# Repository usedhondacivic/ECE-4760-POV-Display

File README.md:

# ECE-4760 Final Project: Persistence of Vision Display
A persistence of vision display constructed from scratch using the Raspberry Pi Pico W microcontroller. Runs at 30 FPS with full RGB color and streams images over wifi.

Created by: Michael Crum (mmc323@cornell.edu), Joseph Horwitz (jah569@cornell.edu), Rabail Makhdoom (rm857@cornell.edu)

Read the write up: https://michael-crum.com/pov_display/

Project structure:
 - /PICO
	 - main.c
		 - Code entry point on the pico
	 - /drivers/apa102
		- Driver for the SPI based APA102 LEDs
	 - /utils/picow_tcp_client.c
		 - Driver for the TCP client
 - /PYTHON
	 - wifi.py
		 - TCP server for sending image data
- /new_python
	- New experimental python setup, including a browser based interface and support for most image types including gif's
	- web_server.py
		- Entry point for the program, launches the webserver which serves the web interface on localhost port 8080 (localhost:8080 in your web browser)
	- tcp_server.py
		- Handles connecting to the display over TCP, and sending arbitry data over the connection
	- file_translation.py
		- Translates image data to a radial RGB format used by the display
	- display_driver.py
		- Handles the transition from a file name to the proper byte format, then sends packets to the display using functions from tcp_server.py
	-  index.html
		- The html file served by the browser client in web_server.py

 - /HARDWARE
	 - /CAD
		 - STL files for 3D printing the mechanical structure
	 - /ELECTRICAL
		 - KiCad project files for the rotor and control board PCBs

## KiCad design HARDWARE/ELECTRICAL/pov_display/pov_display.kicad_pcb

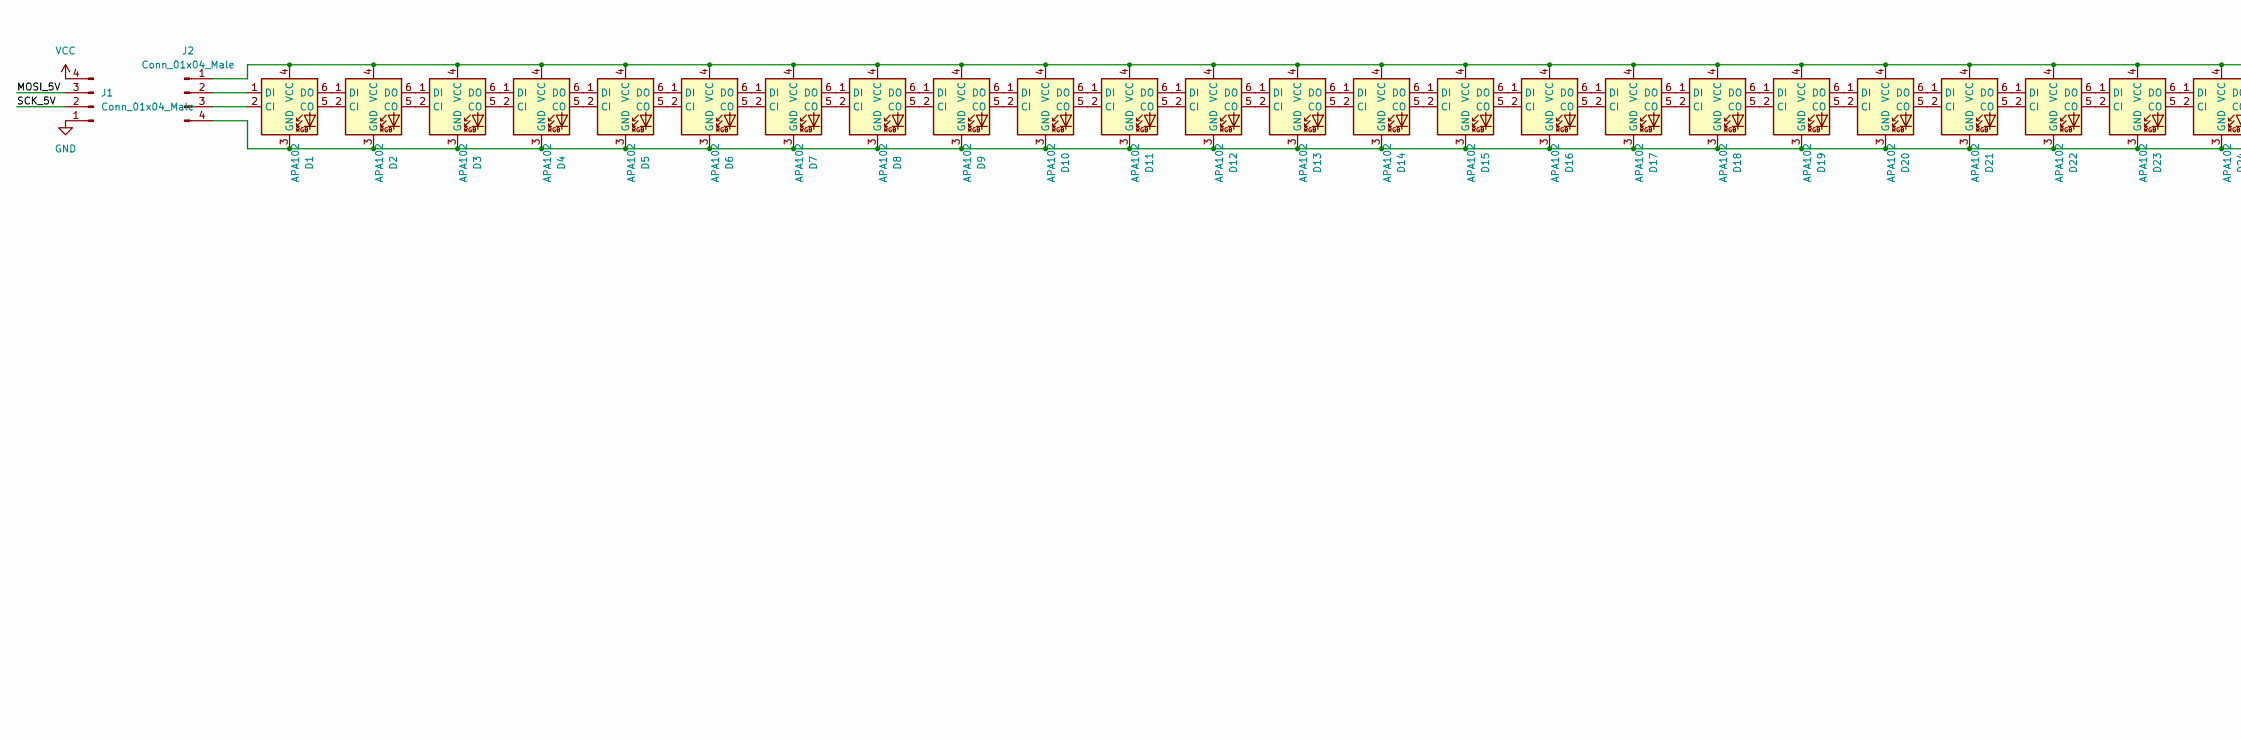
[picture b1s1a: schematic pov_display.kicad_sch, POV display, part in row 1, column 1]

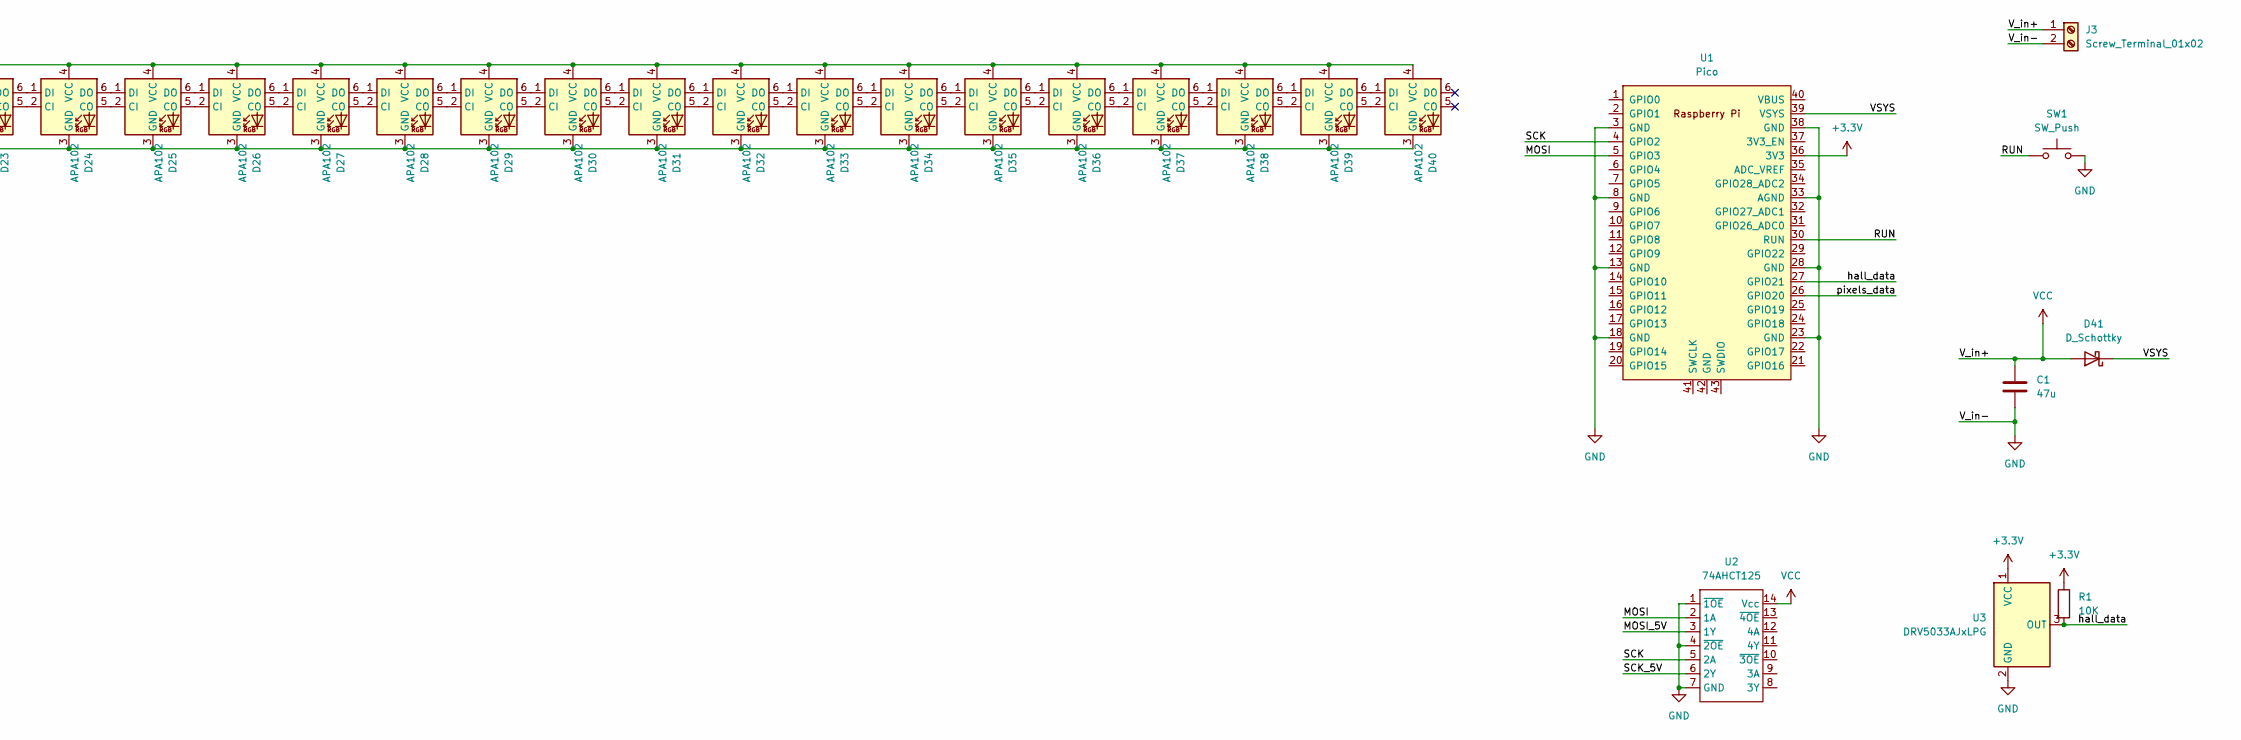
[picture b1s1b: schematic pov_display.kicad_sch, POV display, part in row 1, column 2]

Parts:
C1: 47u; C_Rect_L7.0mm_W2.5mm_P5.00mm
D1, D2, D3, D4, D5, D6, D7, D8, D9, D10, D11, D12, D13, D14, D15, D16, D17, D18, D19, D20, D21, D22, D23, D24, D25, D26, D27, D28, D29, D30, D31, D32, D33, D34, D35, D36, D37, D38, D39, D40: APA102; LED_RGB_5050-6
D41: D_Schottky; D_DO-201AE_P3.81mm_Vertical_AnodeUp
J1, J2: Conn_01x04_Male; PinHeader_1x04_P2.54mm_Vertical
J3: Screw_Terminal_01x02; TerminalBlock_Phoenix_PT-1,5-2-5.0-H_1x02_P5.00mm_Horizontal
R1: 10K; R_Axial_DIN0207_L6.3mm_D2.5mm_P10.16mm_Horizontal
SW1: SW_Push; SW_PUSH_6mm
U1: Pico; RPi_Pico_SMD_TH
U2: 74AHCT125; 74AHCT125-PDIP
U3: DRV5033AJxLPG; TO-92_Inline_Wide

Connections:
+3.3V: R1.1, U1.36 (3V3), U3.1 (VCC)
/MOSI: U1.5 (GPIO3), U2.2 (1A)
/MOSI_5V: J1.3, U2.3 (1Y)
/RUN: SW1.1, U1.30 (RUN)
/SCK: U1.4 (GPIO2), U2.5 (2A)
/SCK_5V: J1.2, U2.6 (2Y)
/VSYS: D41.1 (K), U1.39 (VSYS)
/hall_data: R1.2, U1.27 (GPIO21), U3.3 (OUT)
/pixels_data: U1.26 (GPIO20)
GND: C1.2, J1.1, J3.2, SW1.2, U1.3 (GND), U1.8 (GND), U1.13 (GND), U1.18 (GND), U1.23 (GND), U1.28 (GND), U1.33 (AGND), U1.38 (GND), U2.1 (~1OE), U2.4 (~2OE), U2.7 (GND), U3.2 (GND)
unnamed: D1.1 (DI), J2.2
unnamed: D1.2 (CI), J2.3
unnamed: D1.3 (GND), D2.3 (GND), D3.3 (GND), D4.3 (GND), D5.3 (GND), D6.3 (GND), D7.3 (GND), D8.3 (GND), D9.3 (GND), D10.3 (GND), D11.3 (GND), D12.3 (GND), D13.3 (GND), D14.3 (GND), D15.3 (GND), D16.3 (GND), D17.3 (GND), D18.3 (GND), D19.3 (GND), D20.3 (GND), D21.3 (GND), D22.3 (GND), D23.3 (GND), D24.3 (GND), D25.3 (GND), D26.3 (GND), D27.3 (GND), D28.3 (GND), D29.3 (GND), D30.3 (GND), D31.3 (GND), D32.3 (GND), D33.3 (GND), D34.3 (GND), D35.3 (GND), D36.3 (GND), D37.3 (GND), D38.3 (GND), D39.3 (GND), D40.3 (GND), J2.4
unnamed: D1.4 (VCC), D2.4 (VCC), D3.4 (VCC), D4.4 (VCC), D5.4 (VCC), D6.4 (VCC), D7.4 (VCC), D8.4 (VCC), D9.4 (VCC), D10.4 (VCC), D11.4 (VCC), D12.4 (VCC), D13.4 (VCC), D14.4 (VCC), D15.4 (VCC), D16.4 (VCC), D17.4 (VCC), D18.4 (VCC), D19.4 (VCC), D20.4 (VCC), D21.4 (VCC), D22.4 (VCC), D23.4 (VCC), D24.4 (VCC), D25.4 (VCC), D26.4 (VCC), D27.4 (VCC), D28.4 (VCC), D29.4 (VCC), D30.4 (VCC), D31.4 (VCC), D32.4 (VCC), D33.4 (VCC), D34.4 (VCC), D35.4 (VCC), D36.4 (VCC), D37.4 (VCC), D38.4 (VCC), D39.4 (VCC), D40.4 (VCC), J2.1
unnamed: D1.5 (CO), D2.2 (CI)
unnamed: D1.6 (DO), D2.1 (DI)
unnamed: D2.5 (CO), D3.2 (CI)
unnamed: D2.6 (DO), D3.1 (DI)
unnamed: D3.5 (CO), D4.2 (CI)
unnamed: D3.6 (DO), D4.1 (DI)
unnamed: D4.5 (CO), D5.2 (CI)
unnamed: D4.6 (DO), D5.1 (DI)
unnamed: D5.5 (CO), D6.2 (CI)
unnamed: D5.6 (DO), D6.1 (DI)
unnamed: D6.5 (CO), D7.2 (CI)
unnamed: D6.6 (DO), D7.1 (DI)
unnamed: D7.5 (CO), D8.2 (CI)
unnamed: D7.6 (DO), D8.1 (DI)
unnamed: D8.5 (CO), D9.2 (CI)
unnamed: D8.6 (DO), D9.1 (DI)
unnamed: D9.6 (DO), D10.1 (DI)
unnamed: D9.5 (CO), D10.2 (CI)
unnamed: D10.5 (CO), D11.2 (CI)
unnamed: D10.6 (DO), D11.1 (DI)
unnamed: D11.5 (CO), D12.2 (CI)
unnamed: D11.6 (DO), D12.1 (DI)
unnamed: D12.5 (CO), D13.2 (CI)
unnamed: D12.6 (DO), D13.1 (DI)
unnamed: D13.5 (CO), D14.2 (CI)
unnamed: D13.6 (DO), D14.1 (DI)
unnamed: D14.5 (CO), D15.2 (CI)
unnamed: D14.6 (DO), D15.1 (DI)
unnamed: D15.5 (CO), D16.2 (CI)
unnamed: D15.6 (DO), D16.1 (DI)
unnamed: D16.5 (CO), D17.2 (CI)
unnamed: D16.6 (DO), D17.1 (DI)
unnamed: D17.5 (CO), D18.2 (CI)
unnamed: D17.6 (DO), D18.1 (DI)
unnamed: D18.5 (CO), D19.2 (CI)
unnamed: D18.6 (DO), D19.1 (DI)
unnamed: D19.5 (CO), D20.2 (CI)
unnamed: D19.6 (DO), D20.1 (DI)
unnamed: D20.5 (CO), D21.2 (CI)
unnamed: D20.6 (DO), D21.1 (DI)
unnamed: D21.5 (CO), D22.2 (CI)
unnamed: D21.6 (DO), D22.1 (DI)
unnamed: D22.5 (CO), D23.2 (CI)
unnamed: D22.6 (DO), D23.1 (DI)
unnamed: D23.5 (CO), D24.2 (CI)
unnamed: D23.6 (DO), D24.1 (DI)
unnamed: D24.5 (CO), D25.2 (CI)
unnamed: D24.6 (DO), D25.1 (DI)
unnamed: D25.5 (CO), D26.2 (CI)
unnamed: D25.6 (DO), D26.1 (DI)
unnamed: D26.5 (CO), D27.2 (CI)
unnamed: D26.6 (DO), D27.1 (DI)
unnamed: D27.5 (CO), D28.2 (CI)
unnamed: D27.6 (DO), D28.1 (DI)
unnamed: D28.5 (CO), D29.2 (CI)
unnamed: D28.6 (DO), D29.1 (DI)
unnamed: D29.5 (CO), D30.2 (CI)
unnamed: D29.6 (DO), D30.1 (DI)
unnamed: D30.5 (CO), D31.2 (CI)
unnamed: D30.6 (DO), D31.1 (DI)
unnamed: D31.5 (CO), D32.2 (CI)
unnamed: D31.6 (DO), D32.1 (DI)
unnamed: D32.5 (CO), D33.2 (CI)
unnamed: D32.6 (DO), D33.1 (DI)
unnamed: D33.5 (CO), D34.2 (CI)
unnamed: D33.6 (DO), D34.1 (DI)
unnamed: D34.5 (CO), D35.2 (CI)
unnamed: D34.6 (DO), D35.1 (DI)
unnamed: D35.5 (CO), D36.2 (CI)
unnamed: D35.6 (DO), D36.1 (DI)
unnamed: D36.5 (CO), D37.2 (CI)
unnamed: D36.6 (DO), D37.1 (DI)
unnamed: D37.5 (CO), D38.2 (CI)
unnamed: D37.6 (DO), D38.1 (DI)
unnamed: D38.5 (CO), D39.2 (CI)
unnamed: D38.6 (DO), D39.1 (DI)
unnamed: D39.5 (CO), D40.2 (CI)
unnamed: D39.6 (DO), D40.1 (DI)
VCC: C1.1, D41.2 (A), J1.4, J3.1, U2.14 (Vcc)

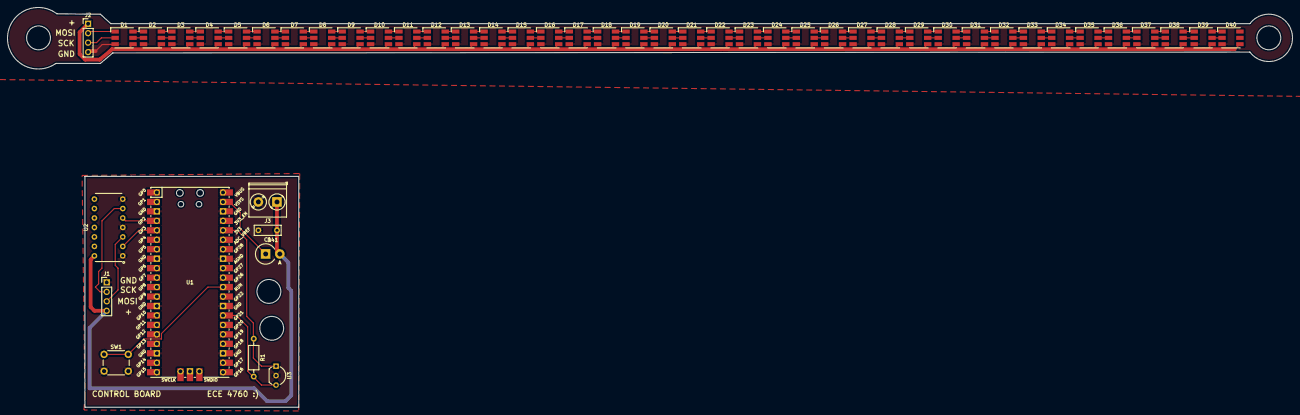
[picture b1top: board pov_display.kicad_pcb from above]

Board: 2 copper layers, 345.0 x 16.5 mm, 50 parts (0 on the bottom side), 92 nets.

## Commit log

2022-11-02 hello world
2022-11-02 Setup build path ect
2022-11-02 Read mes
2022-11-02 updated build path added ws2812 driver
2022-11-02 Fixed build
2022-11-02 Fixed ws2812 driver
2022-11-02 Fixes
2022-11-09 Add ECAD files
2022-11-11 wifi working
2022-11-11 Added apa102 driver
2022-11-14 Added full strip command
2022-11-14 Color order fix
2022-11-14 WiFi getting closer
2022-11-15 wifi seems to work, haven't tested with real photos though.
2022-11-16 WiFi sending images!
2022-11-16 Working Hall Sensor
2022-11-18 Added pixel effects
2022-11-18 Fixed merge issues Fixed bugs with apa driver
2022-12-02 Fixed issue with tcp
2022-12-04 First working tests.
2022-12-04 Turn off PICO status LED
2022-12-05 IT WORKS
2022-12-06 Hall works!
2022-12-06 added photos and updated send options
2022-12-06 Working?
2022-12-06 bird slow
2022-12-06 Demo code
2022-12-07 Updated schematic for correct silkscreen labels
2022-12-07 Added 3D Print files
2022-12-07 Banner photo
2022-12-07 Smaller banner
2022-12-07 Init pages
2022-12-07 Fix image
2022-12-07 Cleared old docs
2022-12-07 New theme
2022-12-07 I can't spell
2022-12-07 New workflow
2022-12-07 Added url
2022-12-07 Need the /?
2022-12-07 test
2022-12-07 Testing
2022-12-07 dude what
2022-12-07 hummm
2022-12-07 uhhhhh
2022-12-07 No double line
2022-12-07 Theme
2022-12-07 ughhhh
2022-12-07 ughhhhhhhh
2022-12-07 boooo
2022-12-07 Rip description
2022-12-07 minimal
2022-12-09 added prompts for convenience
2022-12-12 talked about programming, added a soundbite, and made some edits.
2022-12-12 forgot to save for last push lol
2022-12-12 more edits
2022-12-13 results and conclusion
2022-12-13 Formatting + test local images
2022-12-13 Added to electrical design
2022-12-13 More electrical
2022-12-13 Mechanical stuff
2022-12-13 Added APA driver info
2022-12-13 Added comments
2022-12-13 Safety
2022-12-13 Code description
2022-12-13 Work on conclusion
2022-12-13 Update results of design
2022-12-13 Reorganize
2022-12-13 Formatting
2022-12-14 Organization
2022-12-14 Adding / labeling images
2022-12-14 Adding pics
2022-12-14 python preprocessing
2022-12-14 relative addressing
2022-12-14 Python image preprocessing
2022-12-14 More pictures
2022-12-14 Links to references
2022-12-14 Dog pictures
2022-12-14 Smaller images + grammar
2022-12-14 Spelling + grammar
2022-12-14 Added code for TCP
2022-12-14 Grammar issue
2022-12-20 Web based python interface
2022-12-22 Working on webserver
2022-12-22 Image translation working
2022-12-22 Added data visualization
2022-12-22 TCP sending data
2022-12-22 Fixed USB uart
2022-12-22 Only use one TCP connection, properly handle large data packets
2022-12-22 TPC correctly handling transactions
2022-12-22 Code cleanup
2022-12-22 Better prints
2022-12-23 New TCP working!
2022-12-24 Added lost connection recovery + auto saturation
2022-12-25 Remove debug prints to help framerate
2022-12-29 Work on video support
2023-01-03 Updated readme for new_python
2023-01-03 Fixed bug in file_translation.py related to running that file as the entry point
2023-01-03 Better documentation
2023-01-03 Added proper GIF timing Fixed browser client file type allowance
2023-01-03 Fixed file type rules
2023-01-03 Moved some code between cores Increased resolution to 300 divisions per rotation
2025-02-08 Add fusion archive of cad
